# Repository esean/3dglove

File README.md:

# 3dglove

Virtual reality haptic glove, venture finalist in 2015 Montery Bay Startup Challenge

Software on Mac used the Leap Motion controller to determine user hand location and fed that info into a physics engine to determine where the hand collided with virtual shapes. That collision information was then used to vibrate the glove at the location and with correct collision intensity to provide haptic feedback to user about touching objects in 3D virtual space.

Glove hardware provided 24 points of haptic info per hand (ie, 24 vibrators), driven by a 24-channel 12-bit LED driver TLC5947. Driver updated via FTDI SPI MPSSE cable, shipping 288bits to LED driver at ~100Hz update rate.

https://www.santacruzsentinel.com/2015/04/30/santa-cruz-hopefuls-vie-for-20000-in-startup-challenge/

Another team member posted a video showing the Mac UI and Leap motion controller, but the glove is not being used in this demo,

https://www.youtube.com/watch?v=leHrdxnxjvA

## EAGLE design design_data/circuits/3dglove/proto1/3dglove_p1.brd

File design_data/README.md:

# design_data

Information has been added to Wiki to track progress.

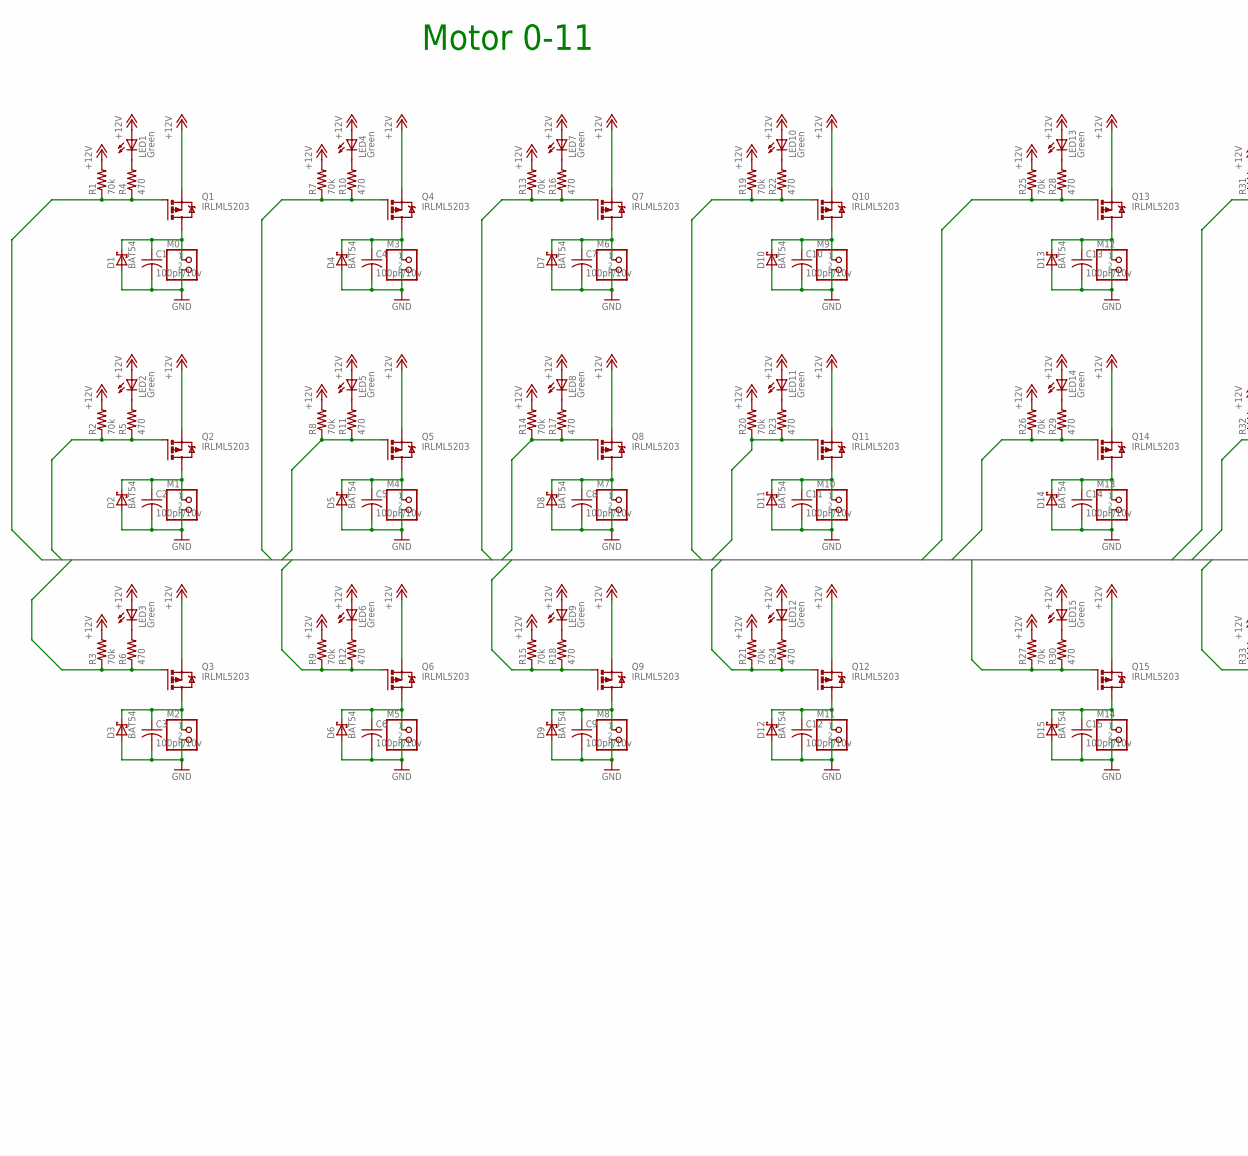
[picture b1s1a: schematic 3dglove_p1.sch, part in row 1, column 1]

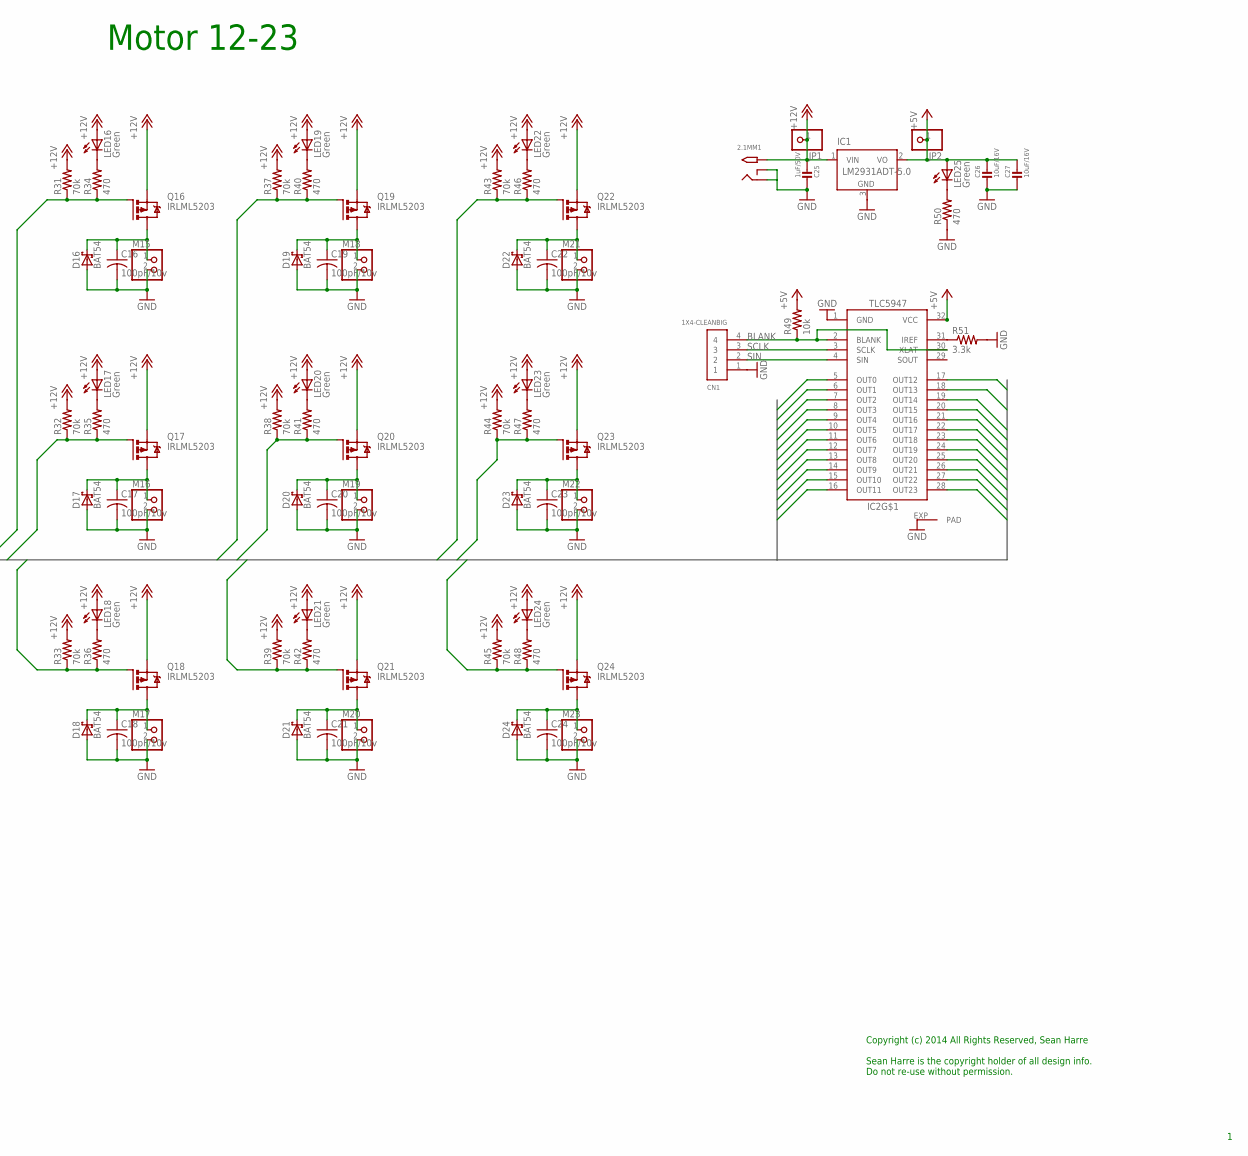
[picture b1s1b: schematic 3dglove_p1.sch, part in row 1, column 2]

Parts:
2.1MM1: 2.1MMJACKTHM; PJ-102A; MPN DC10A
C1, C2, C3, C4, C5, C6, C7, C8, C9, C10, C11, C12, C13, C14, C15, C16, C17, C18, C19, C20, C21, C22, C23, C24: 100pF/10v; C0402; MPN MCMT15N101F100CT
C25: 1uF/50V; 0805; MPN C2012X7R1H105K125AB
C26, C27: 10uF/16V; 0805; MPN C2012X5R1C106K085AC
CN1: 1X4-CLEANBIG; 1X04-CLEANBIG
D1, D2, D3, D4, D5, D6, D7, D8, D9, D10, D11, D12, D13, D14, D15, D16, D17, D18, D19, D20, D21, D22, D23, D24: BAT54; SOT23; MPN BAT54LT1G
IC1: LM2931ADT-5.0; TO252
IC2: TLC5947-DAP; HTSSOP32DAP; MPN TLC5947DAP
JP1, JP2: PINHD-1X1CB; 1X01-CLEANBIG
LED1, LED2, LED3, LED4, LED5, LED6, LED7, LED8, LED9, LED10, LED11, LED12, LED13, LED14, LED15, LED16, LED17, LED18, LED19, LED20, LED21, LED22, LED23, LED24, LED25: Green; CHIP-LED0805
M0, M1, M2, M3, M4, M5, M6, M7, M8, M9, M10, M11, M12, M13, M14, M15, M16, M17, M18, M19, M20, M21, M22, M23: PINHD-1X2; 1X02
Q1, Q2, Q3, Q4, Q5, Q6, Q7, Q8, Q9, Q10, Q11, Q12, Q13, Q14, Q15, Q16, Q17, Q18, Q19, Q20, Q21, Q22, Q23, Q24: IRLML5203; MICRO3; MPN IRLML5203GTRPBF
R1, R2, R3, R7, R8, R9, R13, R14, R15, R19, R20, R21, R25, R26, R27, R31, R32, R33, R37, R38, R39, R43, R44, R45: 70k; R0402; MPN ERJ-2GEJ683X
R4, R5, R6, R10, R11, R12, R16, R17, R18, R22, R23, R24, R28, R29, R30, R34, R35, R36, R40, R41, R42, R46, R47, R48: 470; R1206; MPN MCHP06W2F4700T5E
R49: 10k; R0402; MPN TNPW040210K0BEED
R50: 470; R0402; MPN ERJ-U02F4700X
R51: 3.3k; R0402; MPN M55342K11B3E30STIV

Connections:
+5V: C26.1, C27.1, IC1.2 (VO), IC2.32 (VCC), JP2.1, LED25.A, R49.2
+12V: 2.1MM1.TIP, C25.1, IC1.1 (VIN), JP1.1, LED1.A, LED2.A, LED3.A, LED4.A, LED5.A, LED6.A, LED7.A, LED8.A, LED9.A, LED10.A, LED11.A, LED12.A, LED13.A, LED14.A, LED15.A, LED16.A, LED17.A, LED18.A, LED19.A, LED20.A, LED21.A, LED22.A, LED23.A, LED24.A, Q1.2 (S), Q2.2 (S), Q3.2 (S), Q4.2 (S), Q5.2 (S), Q6.2 (S), Q7.2 (S), Q8.2 (S), Q9.2 (S), Q10.2 (S), Q11.2 (S), Q12.2 (S), Q13.2 (S), Q14.2 (S), Q15.2 (S), Q16.2 (S), Q17.2 (S), Q18.2 (S), Q19.2 (S), Q20.2 (S), Q21.2 (S), Q22.2 (S), Q23.2 (S), Q24.2 (S), R1.2, R2.2, R3.2, R7.2, R8.2, R9.2, R13.2, R14.2, R15.2, R19.2, R20.2, R21.2, R25.2, R26.2, R27.2, R31.2, R32.2, R33.2, R37.2, R38.2, R39.2, R43.2, R44.2, R45.2
BLANK: CN1.4, IC2.2 (BLANK), IC2.30 (XLAT), R49.1
GND: 2.1MM1.RING, 2.1MM1.RING_SW, C1.2, C2.2, C3.2, C4.2, C5.2, C6.2, C7.2, C8.2, C9.2, C10.2, C11.2, C12.2, C13.2, C14.2, C15.2, C16.2, C17.2, C18.2, C19.2, C20.2, C21.2, C22.2, C23.2, C24.2, C25.2, C26.2, C27.2, CN1.1, D1.1 (A), D2.1 (A), D3.1 (A), D4.1 (A), D5.1 (A), D6.1 (A), D7.1 (A), D8.1 (A), D9.1 (A), D10.1 (A), D11.1 (A), D12.1 (A), D13.1 (A), D14.1 (A), D15.1 (A), D16.1 (A), D17.1 (A), D18.1 (A), D19.1 (A), D20.1 (A), D21.1 (A), D22.1 (A), D23.1 (A), D24.1 (A), IC1.3 (GND), IC2.1 (GND), IC2.EXP (PAD), M0.2, M1.2, M2.2, M3.2, M4.2, M5.2, M6.2, M7.2, M8.2, M9.2, M10.2, M11.2, M12.2, M13.2, M14.2, M15.2, M16.2, M17.2, M18.2, M19.2, M20.2, M21.2, M22.2, M23.2, R50.1, R51.2
unnamed: LED25.C, R50.2
unnamed: IC2.31 (IREF), R51.1
unnamed: LED13.C, R28.2
unnamed: C13.1, D13.3 (C), M12.1, Q13.3 (D)
unnamed: LED14.C, R29.2
unnamed: C14.1, D14.3 (C), M13.1, Q14.3 (D)
unnamed: LED15.C, R30.2
unnamed: C15.1, D15.3 (C), M14.1, Q15.3 (D)
unnamed: LED16.C, R34.2
unnamed: C16.1, D16.3 (C), M15.1, Q16.3 (D)
unnamed: LED17.C, R35.2
unnamed: C17.1, D17.3 (C), M16.1, Q17.3 (D)
unnamed: LED18.C, R36.2
unnamed: C18.1, D18.3 (C), M17.1, Q18.3 (D)
unnamed: LED19.C, R40.2
unnamed: C19.1, D19.3 (C), M18.1, Q19.3 (D)
unnamed: LED20.C, R41.2
unnamed: C20.1, D20.3 (C), M19.1, Q20.3 (D)
unnamed: LED21.C, R42.2
unnamed: C21.1, D21.3 (C), M20.1, Q21.3 (D)
unnamed: LED22.C, R46.2
unnamed: C22.1, D22.3 (C), M21.1, Q22.3 (D)
unnamed: LED23.C, R47.2
unnamed: C23.1, D23.3 (C), M22.1, Q23.3 (D)
unnamed: LED24.C, R48.2
unnamed: C24.1, D24.3 (C), M23.1, Q24.3 (D)
unnamed: LED1.C, R4.2
unnamed: C1.1, D1.3 (C), M0.1, Q1.3 (D)
unnamed: LED2.C, R5.2
unnamed: C2.1, D2.3 (C), M1.1, Q2.3 (D)
unnamed: LED3.C, R6.2
unnamed: C3.1, D3.3 (C), M2.1, Q3.3 (D)
unnamed: LED4.C, R10.2
unnamed: C4.1, D4.3 (C), M3.1, Q4.3 (D)
unnamed: LED5.C, R11.2
unnamed: C5.1, D5.3 (C), M4.1, Q5.3 (D)
unnamed: LED6.C, R12.2
unnamed: C6.1, D6.3 (C), M5.1, Q6.3 (D)
unnamed: LED7.C, R16.2
unnamed: C7.1, D7.3 (C), M6.1, Q7.3 (D)
unnamed: LED8.C, R17.2
unnamed: C8.1, D8.3 (C), M7.1, Q8.3 (D)
unnamed: LED9.C, R18.2
unnamed: C9.1, D9.3 (C), M8.1, Q9.3 (D)
unnamed: LED10.C, R22.2
unnamed: C10.1, D10.3 (C), M9.1, Q10.3 (D)
unnamed: LED11.C, R23.2
unnamed: C11.1, D11.3 (C), M10.1, Q11.3 (D)
unnamed: LED12.C, R24.2
unnamed: C12.1, D12.3 (C), M11.1, Q12.3 (D)
OUT0: IC2.5 (OUT0), Q1.1 (G), R1.1, R4.1
OUT1: IC2.6 (OUT1), Q2.1 (G), R2.1, R5.1
OUT2: IC2.7 (OUT2), Q3.1 (G), R3.1, R6.1
OUT3: IC2.8 (OUT3), Q4.1 (G), R7.1, R10.1
OUT4: IC2.9 (OUT4), Q5.1 (G), R8.1, R11.1
OUT5: IC2.10 (OUT5), Q6.1 (G), R9.1, R12.1
OUT6: IC2.11 (OUT6), Q7.1 (G), R13.1, R16.1
OUT7: IC2.12 (OUT7), Q8.1 (G), R14.1, R17.1
OUT8: IC2.13 (OUT8), Q9.1 (G), R15.1, R18.1
OUT9: IC2.14 (OUT9), Q10.1 (G), R19.1, R22.1
OUT10: IC2.15 (OUT10), Q11.1 (G), R20.1, R23.1
OUT11: IC2.16 (OUT11), Q12.1 (G), R21.1, R24.1
OUT12: IC2.17 (OUT12), Q13.1 (G), R25.1, R28.1
OUT13: IC2.18 (OUT13), Q14.1 (G), R26.1, R29.1
OUT14: IC2.19 (OUT14), Q15.1 (G), R27.1, R30.1
OUT15: IC2.20 (OUT15), Q16.1 (G), R31.1, R34.1
OUT16: IC2.21 (OUT16), Q17.1 (G), R32.1, R35.1
OUT17: IC2.22 (OUT17), Q18.1 (G), R33.1, R36.1
OUT18: IC2.23 (OUT18), Q19.1 (G), R37.1, R40.1
OUT19: IC2.24 (OUT19), Q20.1 (G), R38.1, R41.1
OUT20: IC2.25 (OUT20), Q21.1 (G), R39.1, R42.1
OUT21: IC2.26 (OUT21), Q22.1 (G), R43.1, R46.1
OUT22: IC2.27 (OUT22), Q23.1 (G), R44.1, R47.1
OUT23: IC2.28 (OUT23), Q24.1 (G), R45.1, R48.1
SCLK: CN1.3, IC2.3 (SCLK)
SIN: CN1.2, IC2.4 (SIN)

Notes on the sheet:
Motor 0-11
Motor 12-23
Copyright (c) 2014 All Rights Reserved, Sean Harre Sean Harre is the copyright holder of all design info. Do not re-use without permission.

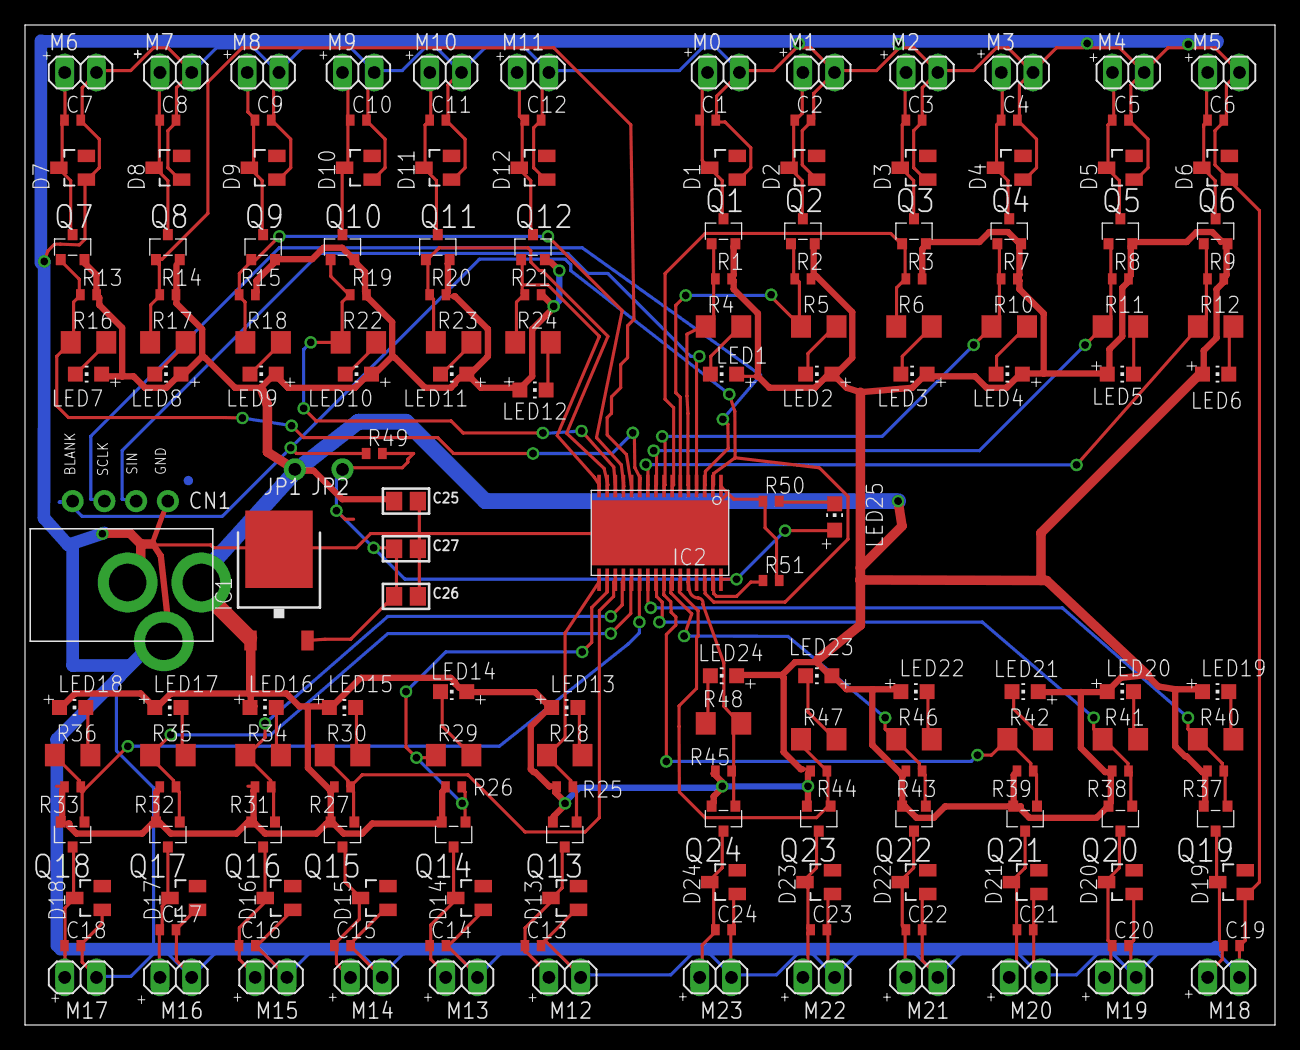
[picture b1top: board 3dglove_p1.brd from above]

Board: 2 copper layers, 100.0 x 80.0 mm, 181 parts (0 on the bottom side), 80 nets.

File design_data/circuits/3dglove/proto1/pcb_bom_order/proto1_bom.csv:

"Qty","Value","Device","Package","Parts","Description","MF","MPN","OC_FARNELL","OC_NEWARK",
"2","","PINHD-1X1CB","1X01-CLEANBIG","JP1; JP2","Pin header 1x1 for 0.1" spacing","","","","",
"24","","PINHD-1X2","1X02","M0; M1; M2; M3; M4; M5; M6; M7; M8; M9; M10; M11; M12; M13; M14; M15; M16; M17; M18; M19; M20; M21; M22; M23","PIN HEADER","","","","",
"24","100pF/10v","C-USC0402","C0402","C1; C2; C3; C4; C5; C6; C7; C8; C9; C10; C11; C12; C13; C14; C15; C16; C17; C18; C19; C20; C21; C22; C23; C24","CAPACITOR; American symbol","","","","",
"1","10k","R-US_R0402","R0402","R49","RESISTOR; American symbol","","","","",
"2","10uF/16V","CAP_CERAMIC0805","0805","C26; C27","Ceramic Capacitors","","","","",
"1","1X4-CLEANBIG","1X4-CLEANBIG","1X04-CLEANBIG","CN1","4-pin connector","","","","",
"1","1uF/50V","CAP_CERAMIC0805","0805","C25","Ceramic Capacitors","","","","",
"1","2.1MMJACKTHM","2.1MMJACKTHM","PJ-102A","2.1MM1","2.1mm x 5.5mm THM DC jack with internal switch. Digikey part #PJ-102A; 4UCON part #05537","","","","",
"1","3.3k","R-US_R0402","R0402","R51","RESISTOR; American symbol","","","","",
"1","470","R-US_R0402","R0402","R50","RESISTOR; American symbol","","","","",
"24","470","R-US_R1206","R1206","R4; R5; R6; R10; R11; R12; R16; R17; R18; R22; R23; R24; R28; R29; R30; R34; R35; R36; R40; R41; R42; R46; R47; R48","RESISTOR; American symbol","","","","",
"24","70k","R-US_R0402","R0402","R1; R2; R3; R7; R8; R9; R13; R14; R15; R19; R20; R21; R25; R26; R27; R31; R32; R33; R37; R38; R39; R43; R44; R45","RESISTOR; American symbol","","","","",
"24","BAT54","BAT54","SOT23","D1; D2; D3; D4; D5; D6; D7; D8; D9; D10; D11; D12; D13; D14; D15; D16; D17; D18; D19; D20; D21; D22; D23; D24","Schottky Diodes","","","","",
"25","Green","LEDCHIP-LED0805","CHIP-LED0805","LED1; LED2; LED3; LED4; LED5; LED6; LED7; LED8; LED9; LED10; LED11; LED12; LED13; LED14; LED15; LED16; LED17; LED18; LED19; LED20; LED21; LED22; LED23; LED24; LED25","LED","","","","",
"24","IRLML5203","IRLML5203","MICRO3","Q1; Q2; Q3; Q4; Q5; Q6; Q7; Q8; Q9; Q10; Q11; Q12; Q13; Q14; Q15; Q16; Q17; Q18; Q19; Q20; Q21; Q22; Q23; Q24","HEXFET P-Channel Power MOSFET","","","","",
"1","LM2931ADT-5.0","LM2936DT-3.3","TO252","IC1","Ultra-Low Quiescent Current LDO Voltage Regulator","","LM2936DT-3.3.","1286863","26M0361",
"1","TLC5947-DAP","TLC5947-DAP","HTSSOP32DAP","IC2","","","","","",

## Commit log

2018-10-27 import
2018-10-30 dont need anymore

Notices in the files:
parts and their libraries:
microbuilder: This work is placed in the public domain, and may be freely used for commercial and non-commercial work with the following conditions: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
